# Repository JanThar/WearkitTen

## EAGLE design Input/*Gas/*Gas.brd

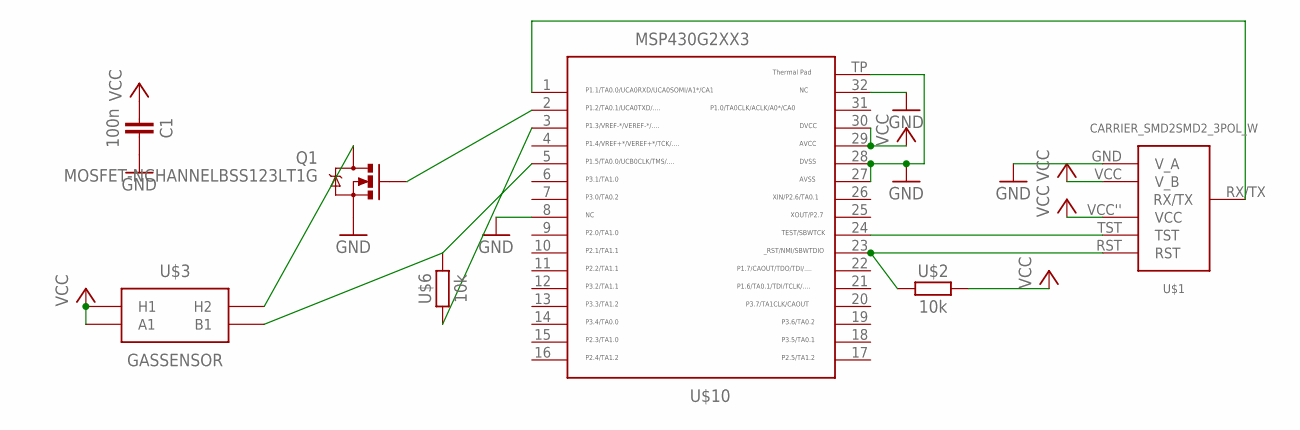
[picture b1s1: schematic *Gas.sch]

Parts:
C1: 100n; 603
Q1: MOSFET-NCHANNELBSS123LT1G; SOT23-3
U$1: CARRIER_SMD2SMD2_3POL_W; CARRIER_SMD2_WIDE_3POL
U$2, U$6: 10k; 603
U$3: GASSENSOR
U$10: MSP430G2553; QFN32

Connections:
GND: C1.2, Q1.2 (S), U$1.GND (V_A), U$10.8, U$10.27, U$10.28, U$10.32, U$10.TP
unnamed: Q1.1 (G), U$10.2
unnamed: U$1.TST, U$10.24
unnamed: U$1.RST, U$2.1, U$10.23
unnamed: Q1.3 (D), U$3.PHB (H2)
unnamed: U$6.1, U$10.3
unnamed: U$1.RX/TX, U$10.1
unnamed: U$3.PB1 (B1), U$6.2, U$10.5
VCC: C1.1, U$1.VCC (V_B), U$1.VCC'' (VCC), U$2.2, U$3.PA1 (A1), U$3.PHA (H1), U$10.29, U$10.30

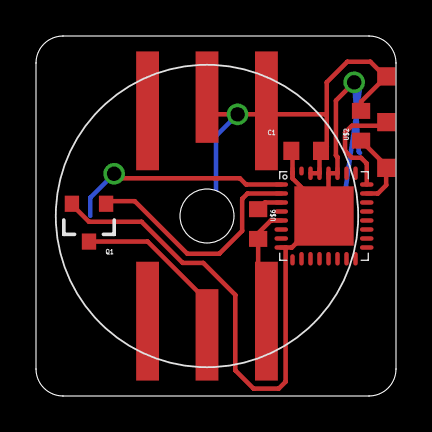
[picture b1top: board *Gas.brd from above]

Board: 2 copper layers, 20.0 x 20.0 mm, 7 parts (0 on the bottom side), 9 nets.

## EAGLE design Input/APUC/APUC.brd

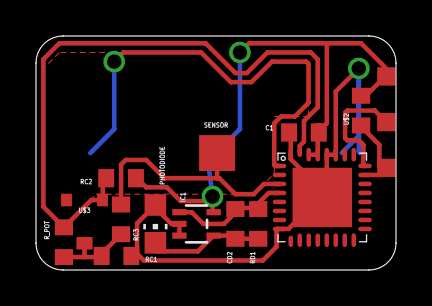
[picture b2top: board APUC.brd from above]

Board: 2 copper layers, 20.0 x 13.0 mm, 14 parts (0 on the bottom side), 10 nets.

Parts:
C1: 100n; 603
CD2: 1p; 603
IC1: AD8519KS; SC70-5
PHOTODIODE: CHIP-LED0805
RC1, RC2: 100k; 603
RC3: 1M; 603
RD1: 10M; 603
R_POT: 100k; 603
SENSOR: TPTP20SQ; TP20SQ
U$1: CARRIER_SMD2SMD2_3POL; CARRIER_SMD2_3POL
U$2: 10k; 603
U$3: 10k; MURATA-PVZ
U$10: MSP430G2553; QFN32

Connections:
COMP_A: RC3.2, SENSOR.TP, U$10.3
COMP_B: RC2.2, R_POT.1, U$3.P$1, U$10.31
GND: C1.2, IC1.2, IC1.3, PHOTODIODE.A, RC1.2, U$1.GND, U$10.8, U$10.27, U$10.28, U$10.32, U$10.TP
LIGHT: CD2.2, IC1.1, RD1.2, U$10.4
unnamed: U$1.TST, U$10.24
unnamed: U$1.RST, U$2.1, U$10.23
unnamed: CD2.1, IC1.4, PHOTODIODE.C, RD1.1
unnamed: U$1.RX/TX, U$10.1
unnamed: RC1.1, RC3.1, R_POT.2, U$3.P$2A
VCC: C1.1, IC1.5, RC2.1, U$1.VCC, U$1.VCC'', U$2.2, U$10.29, U$10.30

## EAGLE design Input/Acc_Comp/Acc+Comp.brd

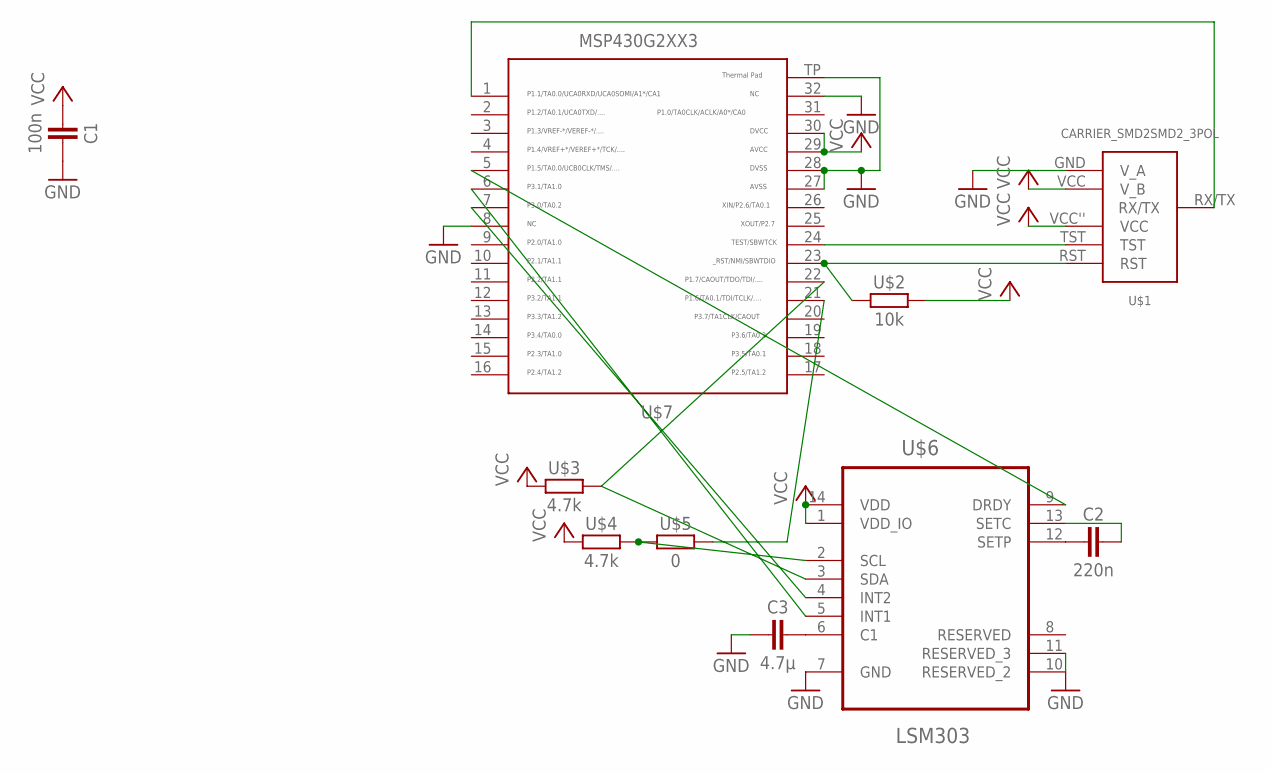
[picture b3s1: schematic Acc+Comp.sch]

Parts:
C1: 100n; 603
C2: 220n; 603
C3: 4.7µ; 603
U$1: CARRIER_SMD2SMD2_3POL; CARRIER_SMD2_3POL
U$2: 10k; 603
U$3, U$4: 4.7k; 603
U$5: 0; 603
U$6: LSM303
U$7: MSP430G2553; QFN32

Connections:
GND: C1.2, C3.1, U$1.GND (V_A), U$6.7 (GND), U$6.10 (RESERVED_2), U$6.11 (RESERVED_3), U$7.8, U$7.27, U$7.28, U$7.32, U$7.TP
unnamed: U$3.2, U$6.3 (SDA), U$7.22
unnamed: U$1.TST, U$7.24
unnamed: U$1.RST, U$2.1, U$7.23
unnamed: U$5.2, U$7.21
unnamed: C2.1, U$6.12 (SETP)
unnamed: C2.2, U$6.13 (SETC)
unnamed: C3.2, U$6.6 (C1)
unnamed: U$1.RX/TX, U$7.1
unnamed: U$6.5 (INT1), U$7.6
unnamed: U$6.4 (INT2), U$7.7
unnamed: U$6.9 (DRDY), U$7.5
unnamed: U$4.2, U$5.1, U$6.2 (SCL)
VCC: C1.1, U$1.VCC (V_B), U$1.VCC'' (VCC), U$2.2, U$3.1, U$4.1, U$6.1 (VDD_IO), U$6.14 (VDD), U$7.29, U$7.30

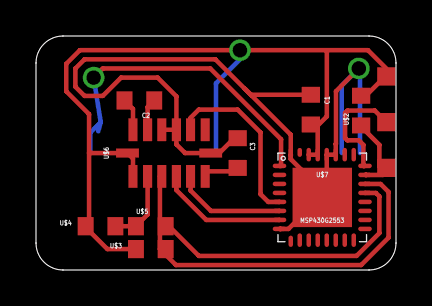
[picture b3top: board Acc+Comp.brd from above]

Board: 2 copper layers, 20.0 x 13.0 mm, 10 parts (0 on the bottom side), 14 nets.

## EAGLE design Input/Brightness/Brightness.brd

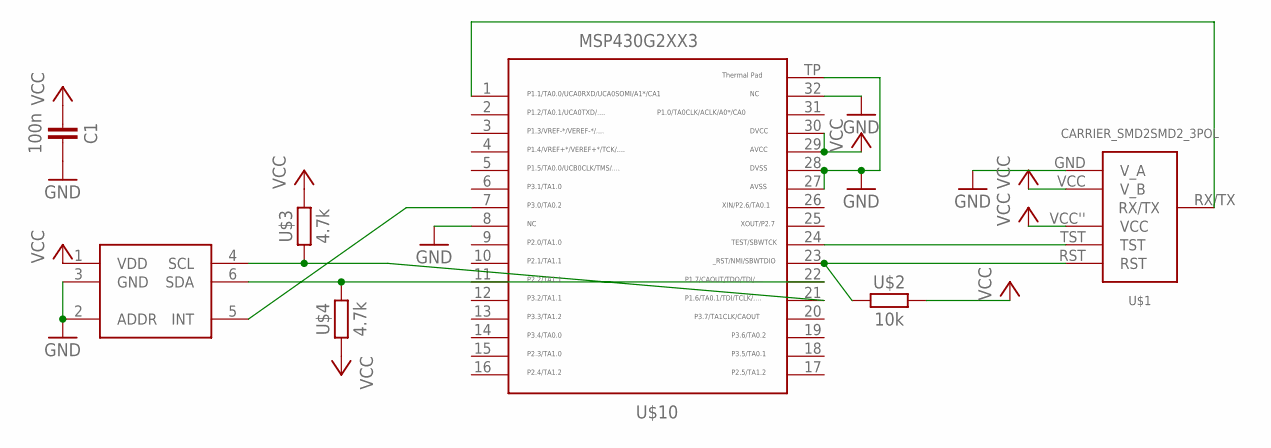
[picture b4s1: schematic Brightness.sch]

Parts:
C1: 100n; 603
U$1: CARRIER_SMD2SMD2_3POL; CARRIER_SMD2_3POL
U$2: 10k; 603
U$3, U$4: 4.7k; 603
U$10: MSP430G2553; QFN32
U$27: TSL2561T

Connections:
GND: C1.2, U$1.GND (V_A), U$10.8, U$10.27, U$10.28, U$10.32, U$10.TP, U$27.2 (ADDR), U$27.3 (GND)
unnamed: U$4.2, U$10.22, U$27.6 (SDA)
unnamed: U$1.TST, U$10.24
unnamed: U$1.RST, U$2.1, U$10.23
unnamed: U$3.1, U$10.21, U$27.4 (SCL)
unnamed: U$10.7, U$27.5 (INT)
unnamed: U$1.RX/TX, U$10.1
VCC: C1.1, U$1.VCC (V_B), U$1.VCC'' (VCC), U$2.2, U$3.2, U$4.1, U$10.29, U$10.30, U$27.1 (VDD)

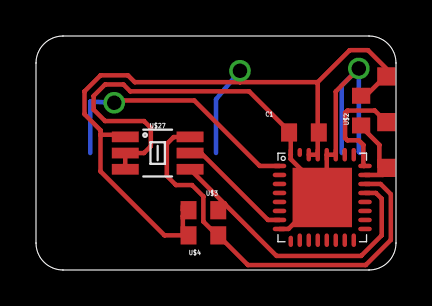
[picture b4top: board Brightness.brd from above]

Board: 2 copper layers, 20.0 x 13.0 mm, 7 parts (0 on the bottom side), 8 nets.

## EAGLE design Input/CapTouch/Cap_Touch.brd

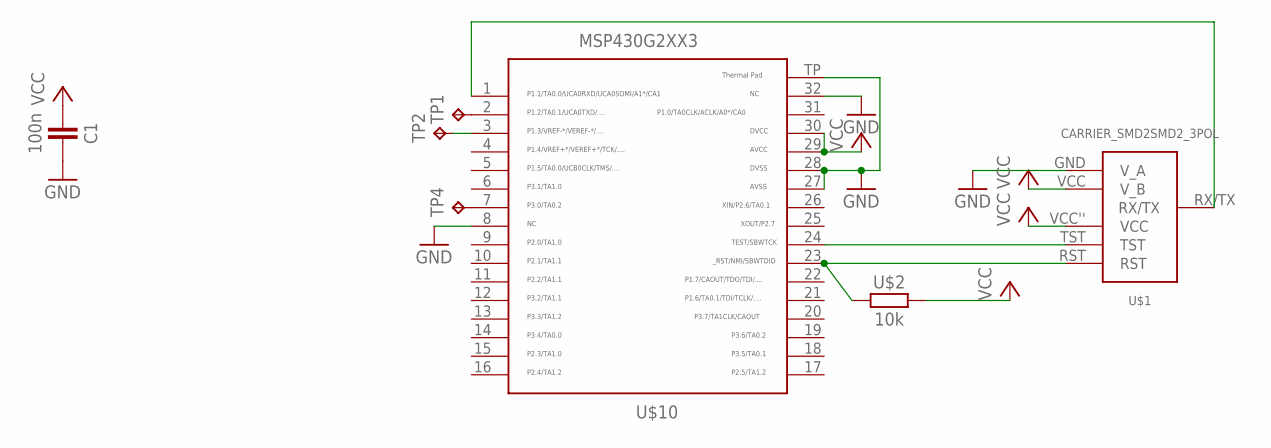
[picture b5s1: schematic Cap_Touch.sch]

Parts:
C1: 100n; 603
TP1, TP2, TP4: TPTP06R; TP06R
U$1: CARRIER_SMD2SMD2_3POL; CARRIER_SMD2_3POL
U$2: 10k; 603
U$10: MSP430G2553; QFN32

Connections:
GND: C1.2, U$1.GND (V_A), U$10.8, U$10.27, U$10.28, U$10.32, U$10.TP
unnamed: TP1.TP, U$10.2
unnamed: U$1.TST, U$10.24
unnamed: U$1.RST, U$2.1, U$10.23
unnamed: TP2.TP, U$10.3
unnamed: TP4.TP, U$10.7
unnamed: U$1.RX/TX, U$10.1
VCC: C1.1, U$1.VCC (V_B), U$1.VCC'' (VCC), U$2.2, U$10.29, U$10.30

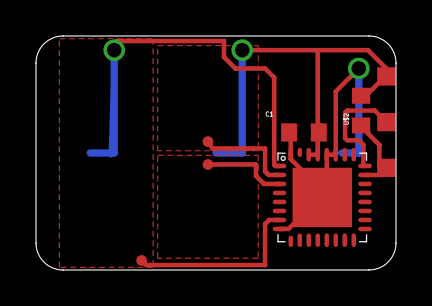
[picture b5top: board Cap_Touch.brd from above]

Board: 2 copper layers, 20.0 x 13.0 mm, 7 parts (0 on the bottom side), 8 nets.

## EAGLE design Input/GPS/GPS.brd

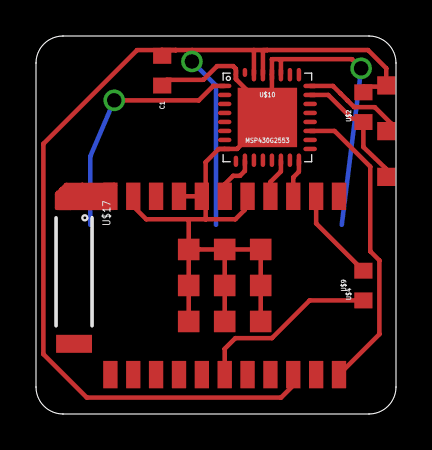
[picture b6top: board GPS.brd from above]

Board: 2 copper layers, 20.0 x 21.0 mm, 7 parts (0 on the bottom side), 12 nets.

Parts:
C1: 100n; 603
U$1: CARRIER_SMD2SMD2_3POL_W; CARRIER_SMD2_WIDE_3POL
U$2, U$4: 10k; 603
U$9: GPS-A2200; A2200
U$10: MSP430G2553; QFN32
U$17: ANTENNA2SMD3; ANTENNA-CHIP4

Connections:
GND: C1.2, U$1.GND, U$9.ANT_GND, U$9.EXTINT2/GPIO8, U$9.GND@1, U$9.GND@2, U$9.GND@3, U$9.GND@4, U$9.GND@5, U$9.GND@6, U$9.GND@7, U$9.GND@8, U$9.GND@9, U$9.GND@10, U$9.GND@11, U$10.8, U$10.27, U$10.28, U$10.32, U$10.TP
unnamed: U$9.TX0, U$10.16
unnamed: U$1.TST, U$10.24
unnamed: U$1.RST, U$2.1, U$10.23
unnamed: U$9.RX0, U$10.14
unnamed: U$9.!RST, U$10.19
unnamed: U$9.ON_OFF, U$10.10
unnamed: U$1.RX/TX, U$10.1
unnamed: U$4.1, U$9.GPIO6
unnamed: U$4.2, U$9.VOUT
unnamed: U$9.ANT_IN, U$17.SIG
VCC: C1.1, U$1.VCC, U$1.VCC'', U$2.2, U$9.VCC, U$10.29, U$10.30

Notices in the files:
parts and their libraries:
SparkFun-DiscreteSemi: Licensing: CC v3.0 Share-Alike You are welcome to use this library for commercial purposes.
